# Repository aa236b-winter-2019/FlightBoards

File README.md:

# FlightBoards
Home of PCB Designs

### Notes: 
* Commit 2427577 Contains Motherboard, Solar Panel X and Solar Panel Y documents that correspond to first revision of these boards
* Commit daf960a contains Solar Panel Z documents that correspond to first revision

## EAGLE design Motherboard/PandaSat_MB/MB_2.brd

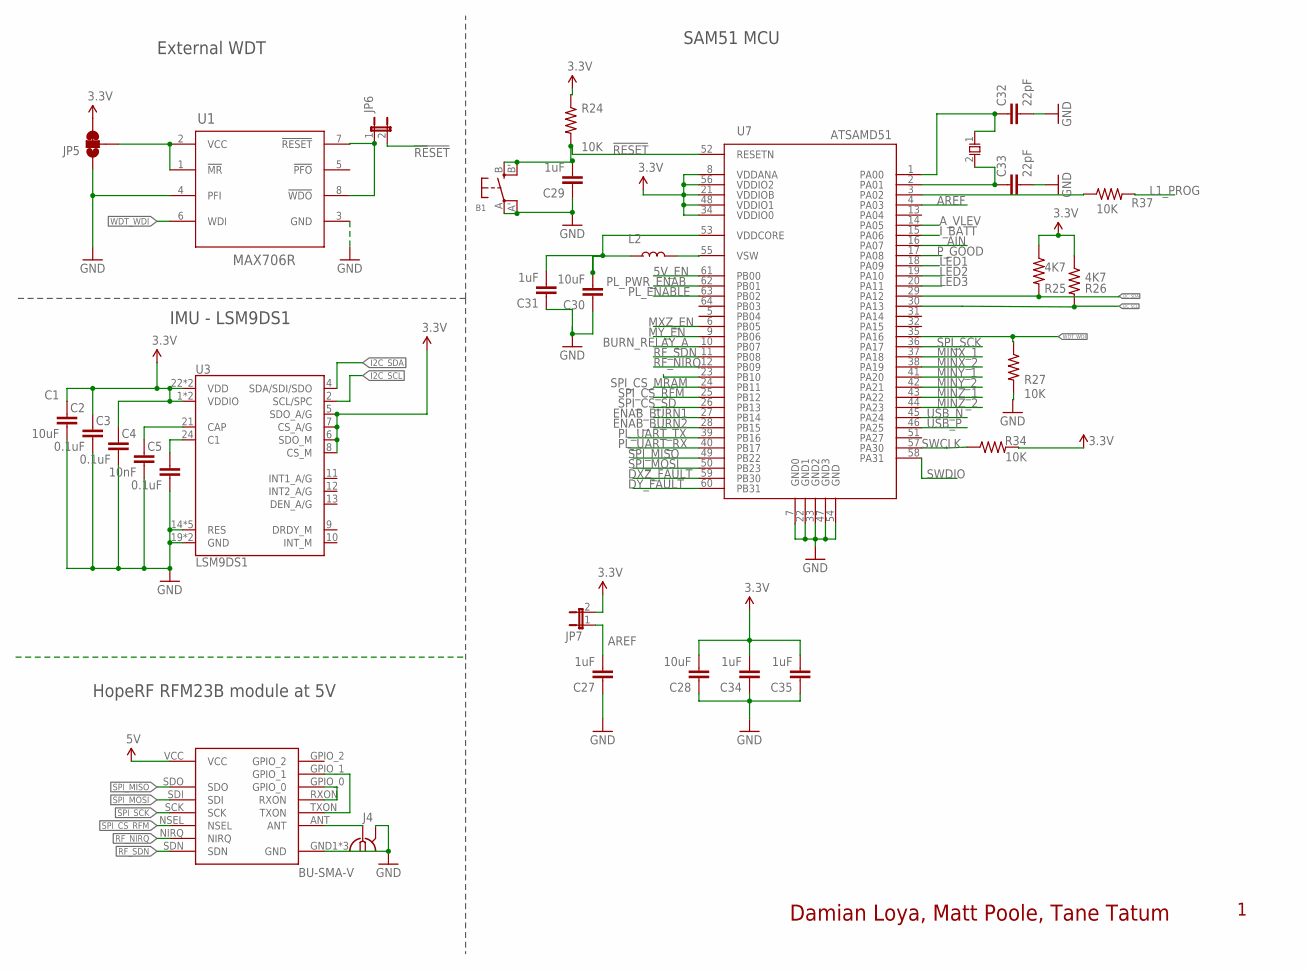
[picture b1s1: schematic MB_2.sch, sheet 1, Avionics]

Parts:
B1: SWITCH_TACT_SMT4.6X2.8; BTN_KMR2_4.6X2.8
C1: 10uF; 0603-CAP
C2, C3, C5: 0.1uF; 0603-CAP
C4: 10nF; 0603-CAP
C27, C29, C31, C34, C35: 1uF; C0603
C28, C30: 10uF; C0603
C32, C33: 22pF; C0603
J4: BU-SMA-V
JP5: JUMPER-PAD-3-2OF3_NC_BY_TRACE_SMALL; PAD-JUMPER-3-2OF3_NC_BY_TRACE_YES_SILK_FULL_BOX
JP6, JP7: JP1E; JP1
L2: 10uH; 1210
R24, R27, R34, R37: 10K; R0603
R25, R26: 4K7; R0603
U1: MAX706R; SO8
U3: LSM9DS1; LGA24-8X4
U5: RFM23BP
U7: ATSAMD51; TQFP-64
X1: ECX-31B

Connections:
3.3V: C1.1, C2.1, C3.1, C28.2, C34.2, C35.2, JP5.3, JP7.2, R24.1, R25.1, R26.1, R34.2, U3.1 (VDDIO), U3.3 (VDDIO), U3.5 (SDO_A/G), U3.6 (SDO_M), U3.7 (CS_A/G), U3.8 (CS_M), U3.22 (VDD), U3.23 (VDD), U7.8 (VDDANA), U7.21 (VDDIOB), U7.34 (VDDIO0), U7.48 (VDDIO1), U7.56 (VDDIO2); also elsewhere on the board
5V: U5.VCC; also elsewhere on the board
5V_EN: U7.61 (PB00); also elsewhere on the board
!RESET: B1.B (S), B1.B' (S1), C29.2, JP6.2, R24.2, U7.52 (RESETN); also elsewhere on the board
AIN: U7.16 (PA07)
AREF: C27.2, JP7.1, U7.4 (PA03)
A_VLEV: U7.14 (PA05); also elsewhere on the board
BURN_RELAY_A: U7.10 (PB07); also elsewhere on the board
DXZ_FAULT: U7.59 (PB30); also elsewhere on the board
DY_FAULT: U7.60 (PB31); also elsewhere on the board
ENAB_BURN1: U7.27 (PB14); also elsewhere on the board
ENAB_BURN2: U7.28 (PB15); also elsewhere on the board
GND: B1.A, B1.A' (P1), C1.2, C2.2, C3.2, C4.2, C5.2, C27.1, C28.1, C29.1, C30.1, C31.1, C32.2, C33.2, C34.1, C35.1, J4.2, J4.3 (2), J4.4 (2), J4.5 (2), JP5.1, R27.2, U1.3 (GND), U1.4 (PFI), U3.14 (RES), U3.15 (RES), U3.16 (RES), U3.17 (RES), U3.18 (RES), U3.19 (GND), U3.20 (GND), U5.GND1 (GND), U5.GND2 (GND), U5.GND3 (GND), U7.7 (GND0), U7.22 (GND1), U7.33 (GND2), U7.47 (GND3), U7.54 (GND); also elsewhere on the board
I2C_SCL: R26.2, U3.2 (SCL/SPC), U7.30 (PA13)
I2C_SDA: R25.2, U3.4 (SDA/SDI/SDO), U7.29 (PA12)
I_BATT: U7.15 (PA06); also elsewhere on the board
L1_PROG: R37.2; also elsewhere on the board
LED1: U7.18 (PA09); also elsewhere on the board
LED2: U7.19 (PA10); also elsewhere on the board
LED3: U7.20 (PA11); also elsewhere on the board
LED4: U7.23 (PB10); also elsewhere on the board
MINX_1: U7.37 (PA18); also elsewhere on the board
MINX_2: U7.38 (PA19); also elsewhere on the board
MINY_1: U7.41 (PA20); also elsewhere on the board
MINY_2: U7.42 (PA21); also elsewhere on the board
MINZ_1: U7.43 (PA22); also elsewhere on the board
MINZ_2: U7.44 (PA23); also elsewhere on the board
MXZ_EN: U7.6 (PB05); also elsewhere on the board
MY_EN: U7.9 (PB06); also elsewhere on the board
unnamed: JP6.1, U1.7 (!RESET), U1.8 (!WDO)
unnamed: C4.1, U3.21 (CAP)
unnamed: C5.1, U3.24 (C1)
unnamed: JP5.2, U1.1 (!MR), U1.2 (VCC)
unnamed: L2.2, U7.55 (VSW)
unnamed: C32.1, U7.1 (PA00), X1.1
unnamed: J4.1, U5.ANT
unnamed: U5.GPIO_0, U5.RXON
unnamed: U5.GPIO_1, U5.TXON
unnamed: C30.2, C31.2, L2.1, U7.53 (VDDCORE)
unnamed: C33.1, U7.2 (PA01), X1.2
unnamed: R37.1, U7.3 (PA02)
PL_ENABLE: U7.63 (PB02); also elsewhere on the board
PL_PWR_ENAB: U7.62 (PB01); also elsewhere on the board
PL_UART_RX: U7.40 (PB17); also elsewhere on the board
PL_UART_TX: U7.39 (PB16); also elsewhere on the board
P_GOOD: U7.17 (PA08); also elsewhere on the board
RF_NIRQ: U5.NIRQ, U7.12 (PB09)
RF_SDN: U5.SDN, U7.11 (PB08)
SPI_CS_MRAM: U7.24 (PB11); also elsewhere on the board
SPI_CS_RFM: U5.NSEL, U7.25 (PB12)
SPI_CS_SD: U7.26 (PB13); also elsewhere on the board
SPI_MISO: U5.SDO, U7.49 (PB22); also elsewhere on the board
SPI_MOSI: U5.SDI, U7.50 (PB23); also elsewhere on the board
SPI_SCK: U5.SCK, U7.36 (PA17); also elsewhere on the board
SWCLK: R34.1, U7.57 (PA30); also elsewhere on the board
SWDIO: U7.58 (PA31); also elsewhere on the board
USB_N: U7.45 (PA24); also elsewhere on the board
USB_P: U7.46 (PA25); also elsewhere on the board
WDT_WDI: R27.1, U1.6 (WDI), U7.35 (PA16)

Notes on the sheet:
IMU - LSM9DS1
External WDT
HopeRF RFM23B module at 5V
SAM51 MCU
Damian Loya, Matt Poole, Tane Tatum

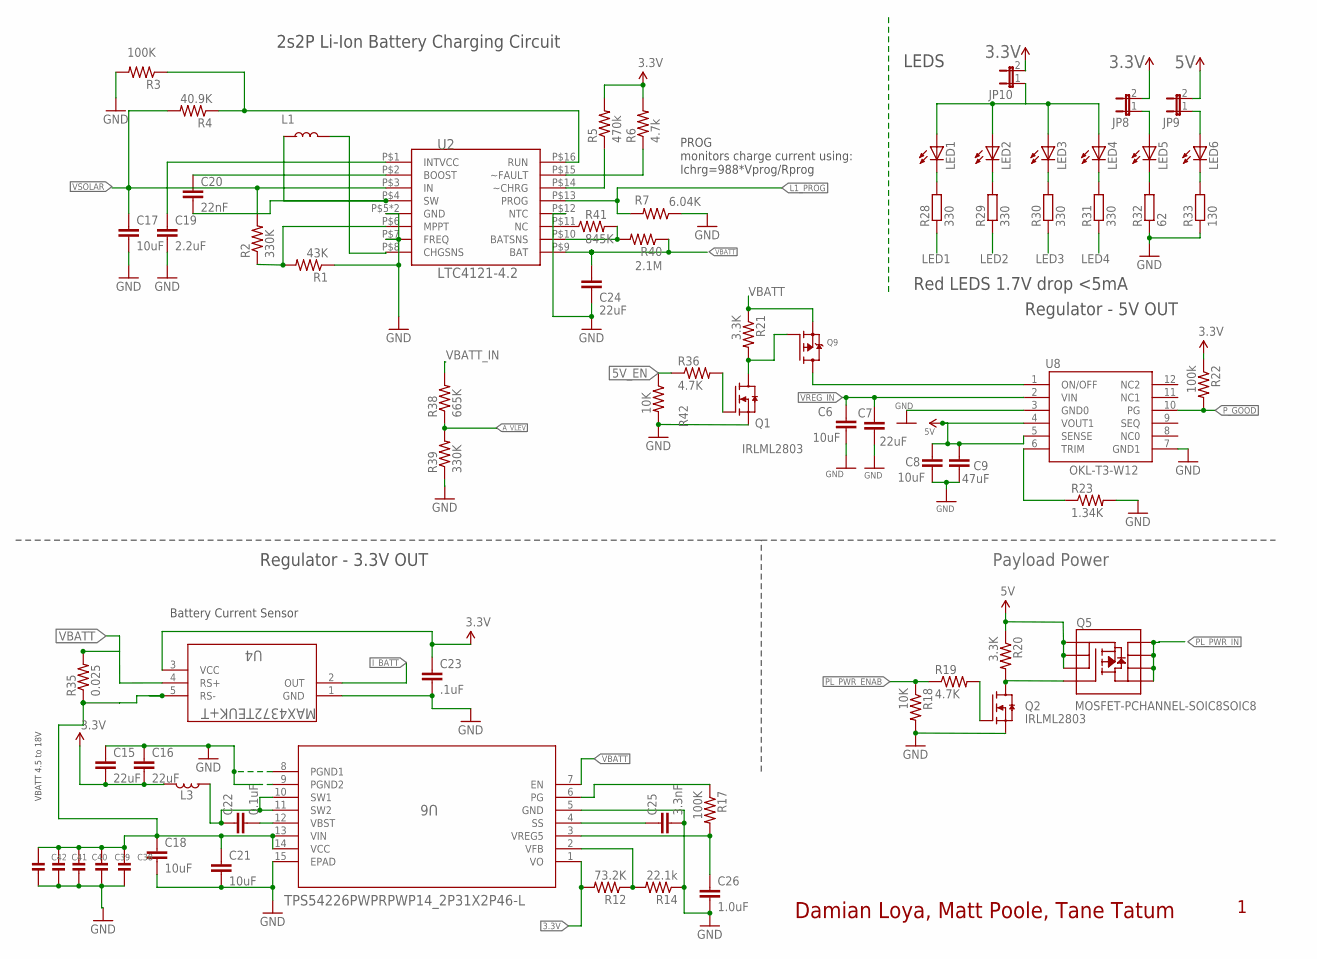
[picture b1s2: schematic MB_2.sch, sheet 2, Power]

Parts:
C6, C8, C17, C18, C21: 10uF; 0603
C7, C24: 22uF; 0603
C9: 47uF; 0603
C15, C16: 22uF; 0805
C19: 2.2uF; 0603
C20: 22nF; 0603
C22: 0.1uF; 0603
C23: .1uF; 0603-CAP
C25: 3.3nF; 0603
C26: 1.0uF; 0603
C38, C39, C40, C41, C42: CAP_CERAMIC1206; 1206
JP8, JP9, JP10: JP1E; JP1
L1: 56uH; 1210
L3: 3.3uH; 1210
LED1, LED2, LED3, LED4, LED5, LED6: LEDCHIP-LED0603; CHIP-LED0603
Q1, Q2: IRLML2803; SOT-23
Q5: MOSFET-PCHANNEL-SOIC8SOIC8; SO08
Q9: MOSFET-PWIDE; SOT23-WIDE
R1: 43K; R0603
R2, R39: 330K; R0603
R3, R17: 100K; R0603
R4: 40.9K; R0603
R5: 470k; R0603
R6: 4.7k; R0603
R7: 6.04K; R0603
R12: 73.2K; R0603
R14: 22.1k; R0603
R18, R42: 10K; R0603
R19, R36: 4.7K; R0603
R20, R21: 3.3K; R0603
R22: 100k; R0603
R23: 1.34K; R0603
R28, R29, R30, R31: 330; R0603
R32: 62; R0603
R33: 130; R0603
R35: 0.025; R1210
R38: 665K; R0603
R40: 2.1M; R0603
R41: 845K; R0603
U2: LTC4121-4.2; QFN-16-PAD
U4: MAX4372TEUK+T; 21-0057F
U6: TPS54226PWPRPWP14_2P31X2P46-L; PWP14_2P31X2P46-L
U8: OKL-T3-W12

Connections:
3.3V: C15.2, C16.2, C23.1, JP8.2, JP10.2, L3.2, R5.2, R6.2, R12.2, R22.1, U4.3 (VCC), U6.1 (VO); also elsewhere on the board
5V: C8.1, C9.1, JP9.2, Q5.1 (S), Q5.2 (S), Q5.3 (S), R20.1, U8.4 (VOUT1), U8.5 (SENSE); also elsewhere on the board
5V_EN: R36.1, R42.1; also elsewhere on the board
A_VLEV: R38.1, R39.2; also elsewhere on the board
GND: C6.2, C7.2, C8.2, C9.2, C15.1, C16.1, C17.2, C18.2, C19.2, C21.2, C23.2, C24.2, C25.2, C26.2, C38.2, C39.2, C40.2, C41.2, C42.2, Q1.2 (S), Q2.2 (S), R1.1, R3.2, R7.1, R14.1, R18.2, R23.2, R32.1, R33.1, R39.1, R42.2, U2.P$5 (GND), U2.P$7 (FREQ), U2.P$12 (NTC), U2.P$17 (GND), U4.1 (GND), U6.5 (GND), U6.8 (PGND1), U6.9 (PGND2), U6.15 (EPAD), U8.3 (GND0), U8.7 (GND1); also elsewhere on the board
I_BATT: U4.2 (OUT); also elsewhere on the board
L1_CHG: R3.1, R4.1, U2.P$16 (RUN)
L1_FAULTN: R6.1, U2.P$15 (~FAULT)
L1_PROG: R7.2, U2.P$13 (PROG); also elsewhere on the board
LED1: R28.1; also elsewhere on the board
LED2: R29.1; also elsewhere on the board
LED3: R30.1; also elsewhere on the board
LED4: R31.1; also elsewhere on the board
unnamed: C22.1, L3.1, U6.10 (SW1), U6.11 (SW2)
unnamed: L1.2, U2.P$8 (CHGSNS)
unnamed: C20.2, L1.1, U2.P$4 (SW)
unnamed: C20.1, U2.P$2 (BOOST)
unnamed: Q2.1 (G), R19.2
unnamed: C19.1, U2.P$1 (INTVCC)
unnamed: Q2.3 (D), Q5.4 (G), R20.2
unnamed: R1.2, R2.1, U2.P$6 (MPPT)
unnamed: C22.2, U6.12 (VBST)
unnamed: R5.1, U2.P$14 (~CHRG)
unnamed: R40.2, R41.2, U2.P$10 (BATSNS)
unnamed: Q1.3 (D), Q9.1 (G), R21.2
unnamed: R23.1, U8.6 (TRIM)
unnamed: Q1.1 (G), R36.2
unnamed: LED1.C, R28.2
unnamed: Q9.3 (D), U8.1 (ON/OFF)
unnamed: LED2.C, R29.2
unnamed: C26.1, R17.2, U6.3 (VREG5)
unnamed: LED3.C, R30.2
unnamed: LED4.C, R31.2
unnamed: LED5.C, R32.2
unnamed: LED6.C, R33.2
unnamed: C25.1, U6.4 (SS)
unnamed: R12.1, R14.2, U6.2 (VFB)
unnamed: JP8.1, LED5.A
unnamed: R41.1, U2.P$11 (NC)
unnamed: JP9.1, LED6.A
unnamed: JP10.1, LED1.A, LED2.A, LED3.A, LED4.A
PGOOD: R17.1, U6.6 (PG)
PL_PWR_ENAB: R18.1, R19.1; also elsewhere on the board
PL_PWR_IN: Q5.5 (D), Q5.6 (D), Q5.7 (D), Q5.8 (D); also elsewhere on the board
P_GOOD: R22.2, U8.10 (PG); also elsewhere on the board
VBATT: C24.1, Q9.2 (S), R21.1, R35.2, R40.1, U2.P$9 (BAT), U4.4 (RS+), U6.7 (EN); also elsewhere on the board
VBATT_IN: R38.2; also elsewhere on the board
VREG_IN: C6.1, C7.1, C18.1, C21.1, C38.1, C39.1, C40.1, C41.1, C42.1, R35.1, U4.5 (RS-), U6.13 (VIN), U6.14 (VCC), U8.2 (VIN)
VSOLAR: C17.1, R2.2, R4.2, U2.P$3 (IN); also elsewhere on the board

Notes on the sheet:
Battery Current Sensor
Payload Power
Regulator - 3.3V OUT
VBATT 4.5 to 18V
Regulator - 5V OUT
2s2P Li-Ion Battery Charging Circuit
PROG monitors charge current using: Ichrg=988*Vprog/Rprog
Damian Loya, Matt Poole, Tane Tatum
LEDS
Red LEDS 1.7V drop <5mA

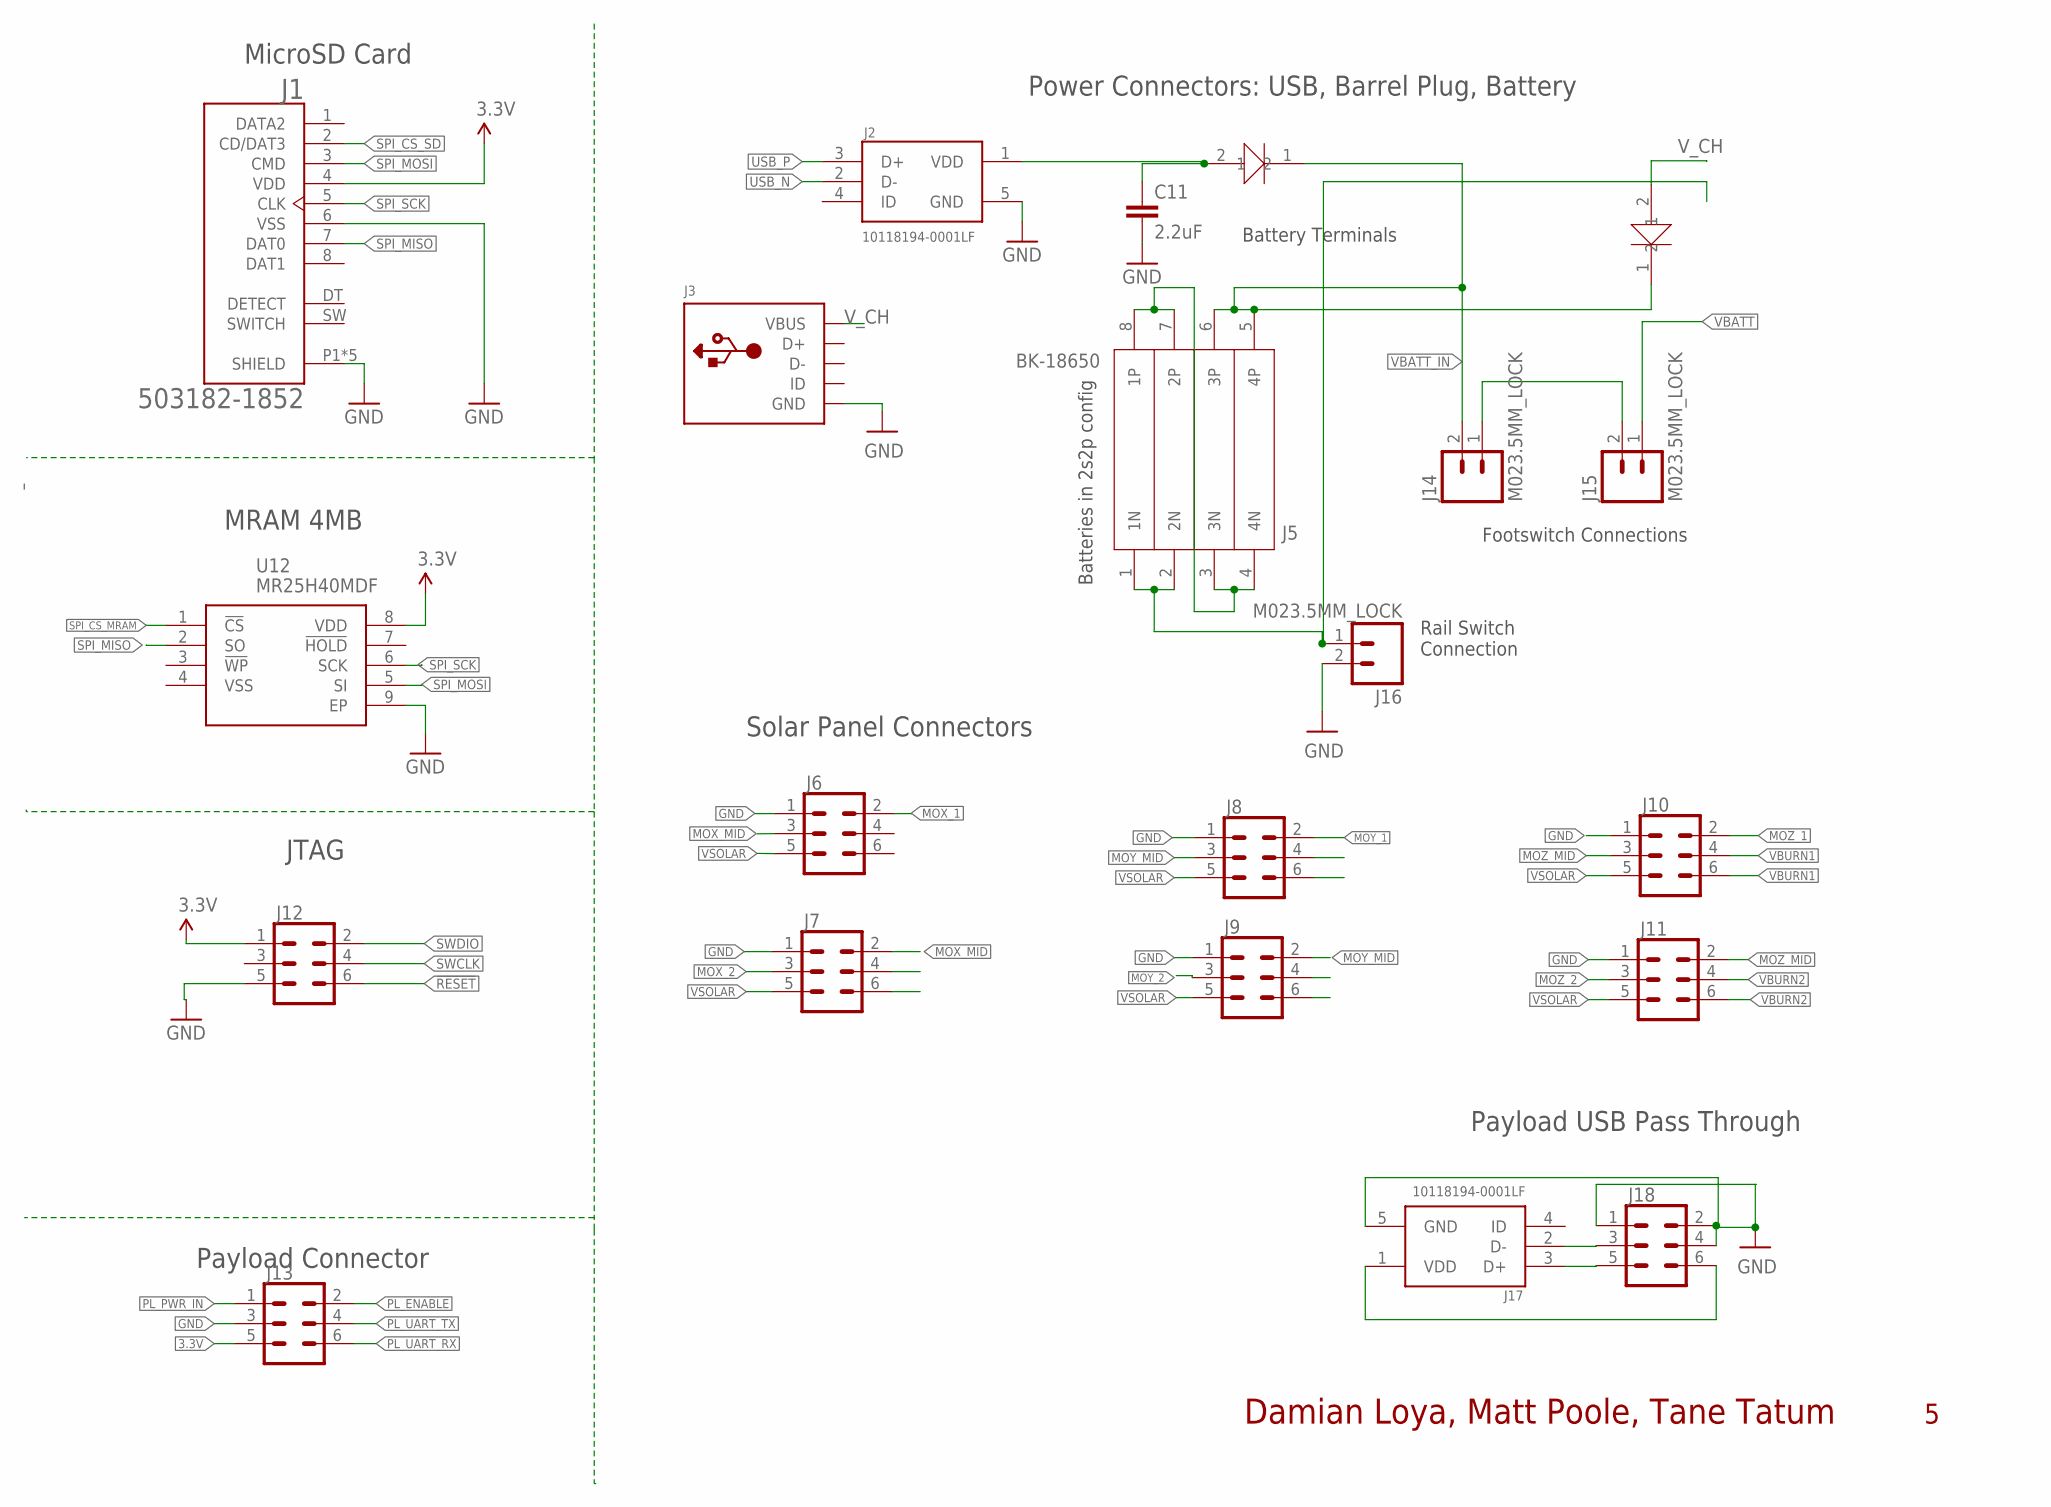
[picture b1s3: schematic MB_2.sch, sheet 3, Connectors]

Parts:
C11: 2.2uF; 0603
D1, D2: RBR5LAM60ATF; SOD-128
J1: 503182-1852; MOLEX_503182-1852
J2, J17: 10118194-0001LF; FRAMATOME_10118194-0001LF
J3: USBMOLEX; USB-MINIB-THM-MOLEX
J5: BK-18650
J6, J7, J8, J9, J10, J11, J12, J13, J18: CONN_03X22X3_SILK_MALE_PTH; 2X3
J14, J15, J16: M023.5MM_LOCK; SCREWTERMINAL-3.5MM-2_LOCK
U12: MR25H40MDF; SON127P600X500X90-9N

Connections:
3.3V: J1.4 (VDD), J12.1, J13.5, U12.8 (VDD); also elsewhere on the board
!RESET: J12.6; also elsewhere on the board
GND: C11.2, J1.6 (VSS), J1.P1 (SHIELD), J1.P2 (SHIELD), J1.P3 (SHIELD), J1.P4 (SHIELD), J1.P5 (SHIELD), J2.5 (GND), J3.GND, J6.1, J7.1, J8.1, J9.1, J10.1, J11.1, J12.5, J13.3, J16.2, J17.5 (GND), J18.1, J18.2, J18.4, U12.9 (EP); also elsewhere on the board
MOX_1: J6.2; also elsewhere on the board
MOX_2: J7.3; also elsewhere on the board
MOX_MID: J6.3, J7.2
MOY_1: J8.2; also elsewhere on the board
MOY_2: J9.3; also elsewhere on the board
MOY_MID: J8.3, J9.2
MOZ_1: J10.2; also elsewhere on the board
MOZ_2: J11.3; also elsewhere on the board
MOZ_MID: J10.3, J11.2
unnamed: J14.1, J15.2
unnamed: C11.1, D2.2, J2.1 (VDD)
unnamed: J17.2 (D-), J18.3
unnamed: J17.3 (D+), J18.5
unnamed: J17.1 (VDD), J18.6
unnamed: J5.3 (3N), J5.4 (4N), J5.7 (2P), J5.8 (1P)
unnamed: J5.1 (1N), J5.2 (2N), J16.1
PL_ENABLE: J13.2; also elsewhere on the board
PL_PWR_IN: J13.1; also elsewhere on the board
PL_UART_RX: J13.6; also elsewhere on the board
PL_UART_TX: J13.4; also elsewhere on the board
SPI_CS_MRAM: U12.1 (!CS); also elsewhere on the board
SPI_CS_SD: J1.2 (CD/DAT3); also elsewhere on the board
SPI_MISO: J1.7 (DAT0), U12.2 (SO); also elsewhere on the board
SPI_MOSI: J1.3 (CMD), U12.5 (SI); also elsewhere on the board
SPI_SCK: J1.5 (CLK), U12.6 (SCK); also elsewhere on the board
SWCLK: J12.4; also elsewhere on the board
SWDIO: J12.2; also elsewhere on the board
USB_N: J2.2 (D-); also elsewhere on the board
USB_P: J2.3 (D+); also elsewhere on the board
VBATT: J15.1; also elsewhere on the board
VBATT_IN: D1.1, D2.1, J5.5 (4P), J5.6 (3P), J14.2; also elsewhere on the board
VBURN1: J10.4, J10.6; also elsewhere on the board
VBURN2: J11.4, J11.6; also elsewhere on the board
VSOLAR: J6.5, J7.5, J8.5, J9.5, J10.5, J11.5; also elsewhere on the board
V_CH: D1.2, J3.VBUS

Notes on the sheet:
Damian Loya, Matt Poole, Tane Tatum
JTAG
Power Connectors: USB, Barrel Plug, Battery
MicroSD Card
MRAM 4MB
Footswitch Connections
Battery Terminals
Rail Switch Connection
Solar Panel Connectors
Payload Connector
Batteries in 2s2p config
Payload USB Pass Through

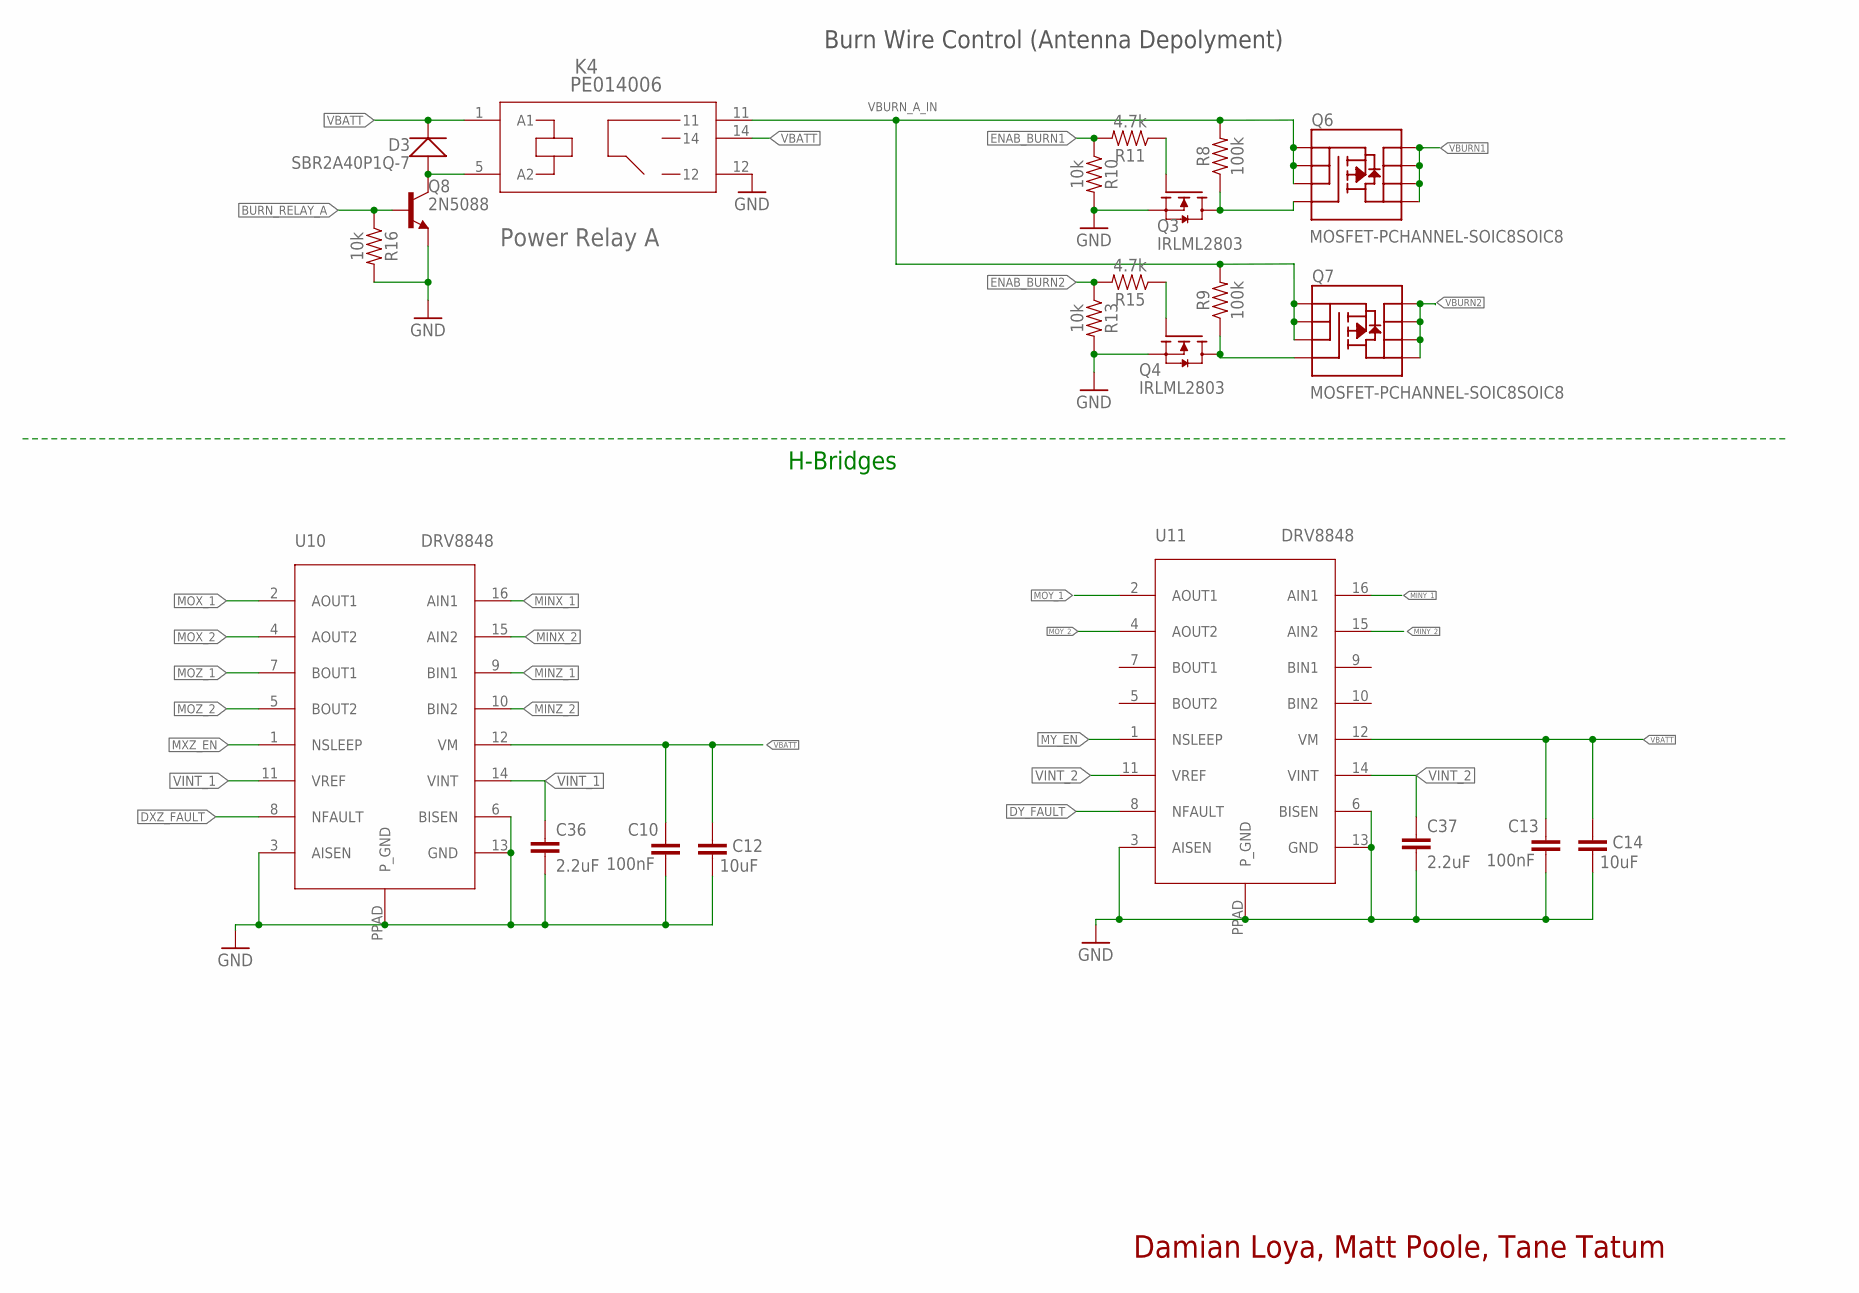
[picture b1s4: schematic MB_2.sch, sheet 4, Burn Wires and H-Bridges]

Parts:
C10, C13: 100nF; 0603
C12, C14: 10uF; 0603
C36, C37: 2.2uF; 0603-CAP; VOLTAGE 6.3V
D3: SBR2A40P1Q-7; PWRDI-123
K4: PE014006; RELAY5-PE_CO
Q3, Q4: IRLML2803; SOT-23
Q6, Q7: MOSFET-PCHANNEL-SOIC8SOIC8; SO08
Q8: 2N5088; SOT23
R8, R9: 100k; 0603
R10, R13, R16: 10k; 0603
R11, R15: 4.7k; 0603
U10, U11: DRV8848; HTSSOP

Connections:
BURN_RELAY_A: Q8.1 (B), R16.1; also elsewhere on the board
DXZ_FAULT: U10.8 (NFAULT); also elsewhere on the board
DY_FAULT: U11.8 (NFAULT); also elsewhere on the board
ENAB_BURN1: R10.1, R11.2; also elsewhere on the board
ENAB_BURN2: R13.1, R15.2; also elsewhere on the board
GND: C10.2, C12.2, C13.2, C14.2, C36.2, C37.2, K4.12, Q3.2 (S), Q4.2 (S), Q8.2 (E), R10.2, R13.2, R16.2, U10.3 (AISEN), U10.6 (BISEN), U10.13 (GND), U10.PPAD (P_GND), U11.3 (AISEN), U11.6 (BISEN), U11.13 (GND), U11.PPAD (P_GND); also elsewhere on the board
MINX_1: U10.16 (AIN1); also elsewhere on the board
MINX_2: U10.15 (AIN2); also elsewhere on the board
MINY_1: U11.16 (AIN1); also elsewhere on the board
MINY_2: U11.15 (AIN2); also elsewhere on the board
MINZ_1: U10.9 (BIN1); also elsewhere on the board
MINZ_2: U10.10 (BIN2); also elsewhere on the board
MOX_1: U10.2 (AOUT1); also elsewhere on the board
MOX_2: U10.4 (AOUT2); also elsewhere on the board
MOY_1: U11.2 (AOUT1); also elsewhere on the board
MOY_2: U11.4 (AOUT2); also elsewhere on the board
MOZ_1: U10.7 (BOUT1); also elsewhere on the board
MOZ_2: U10.5 (BOUT2); also elsewhere on the board
MXZ_EN: U10.1 (NSLEEP); also elsewhere on the board
MY_EN: U11.1 (NSLEEP); also elsewhere on the board
unnamed: Q3.3 (D), Q6.4 (G), R8.1
unnamed: Q3.1 (G), R11.1
unnamed: Q4.1 (G), R15.1
unnamed: D3.A, K4.5 (A2), Q8.3 (C)
unnamed: Q4.3 (D), Q7.4 (G), R9.1
VBATT: C10.1, C12.1, C13.1, C14.1, D3.C, K4.1 (A1), K4.14, U10.12 (VM), U11.12 (VM); also elsewhere on the board
VBURN1: Q6.5 (D), Q6.6 (D), Q6.7 (D), Q6.8 (D); also elsewhere on the board
VBURN2: Q7.5 (D), Q7.6 (D), Q7.7 (D), Q7.8 (D); also elsewhere on the board
VBURN_A_IN: K4.11, Q6.1 (S), Q6.2 (S), Q6.3 (S), Q7.1 (S), Q7.2 (S), Q7.3 (S), R8.2, R9.2
VINT_1: C36.1, U10.11 (VREF), U10.14 (VINT)
VINT_2: C37.1, U11.11 (VREF), U11.14 (VINT)

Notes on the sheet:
Power Relay A
Burn Wire Control (Antenna Depolyment)
H-Bridges
Damian Loya, Matt Poole, Tane Tatum

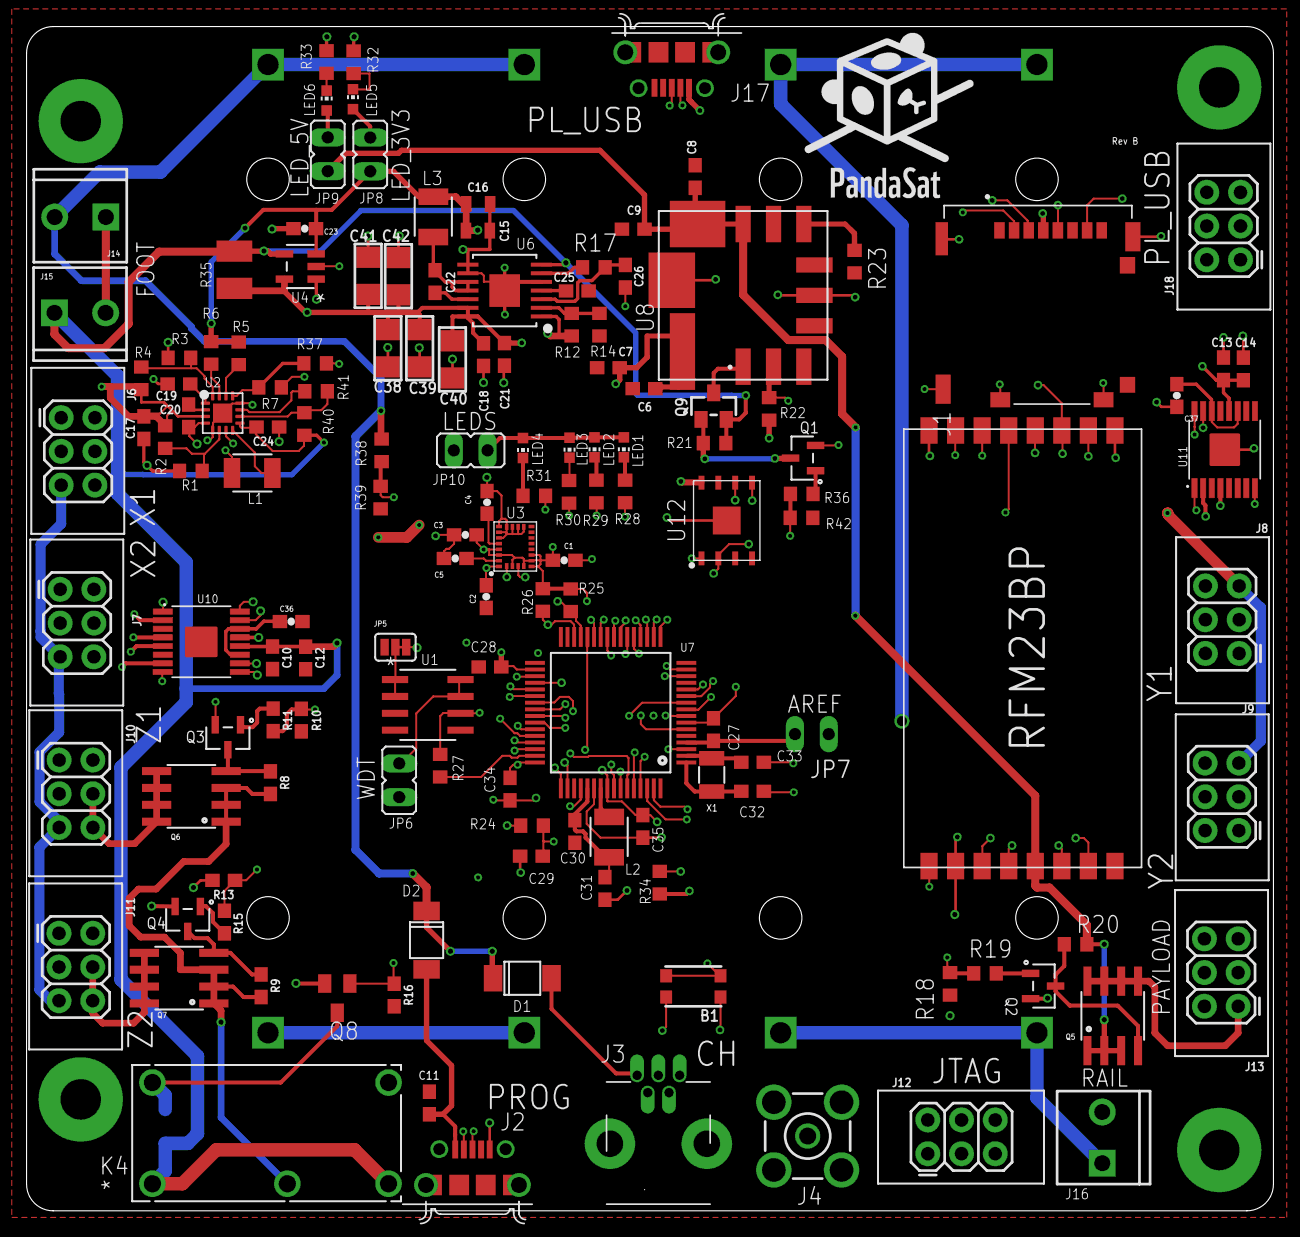
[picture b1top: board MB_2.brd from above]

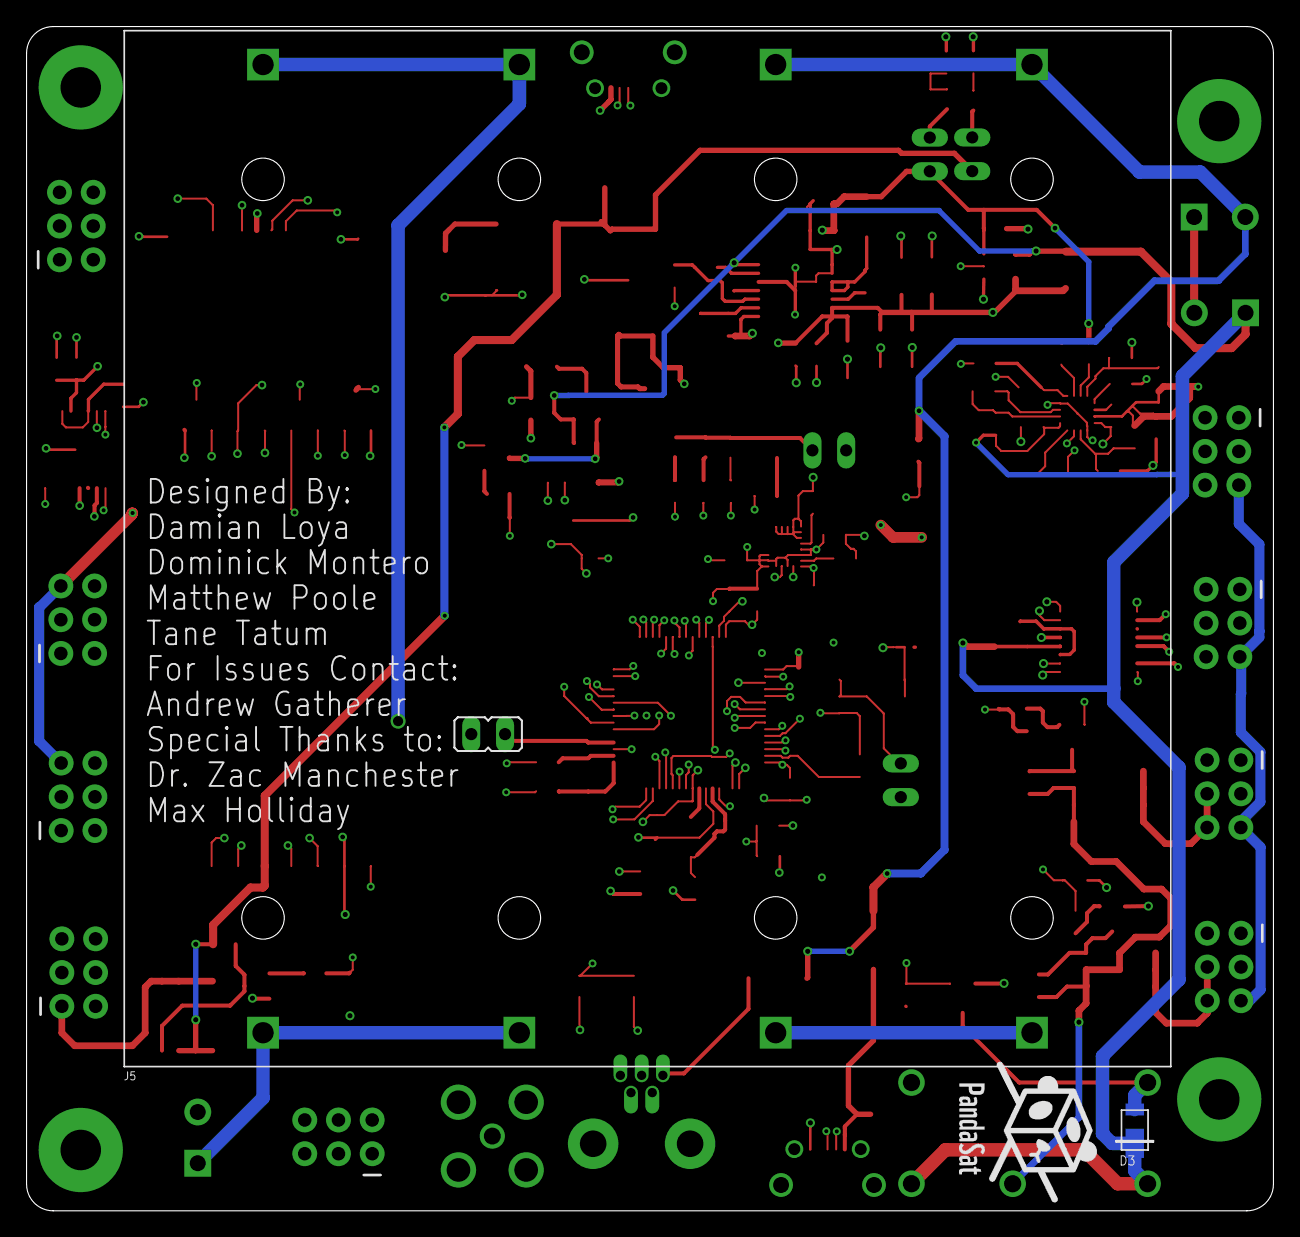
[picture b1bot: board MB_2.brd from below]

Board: 4 copper layers, 93.9 x 89.2 mm, 143 parts (3 on the bottom side), 121 nets.

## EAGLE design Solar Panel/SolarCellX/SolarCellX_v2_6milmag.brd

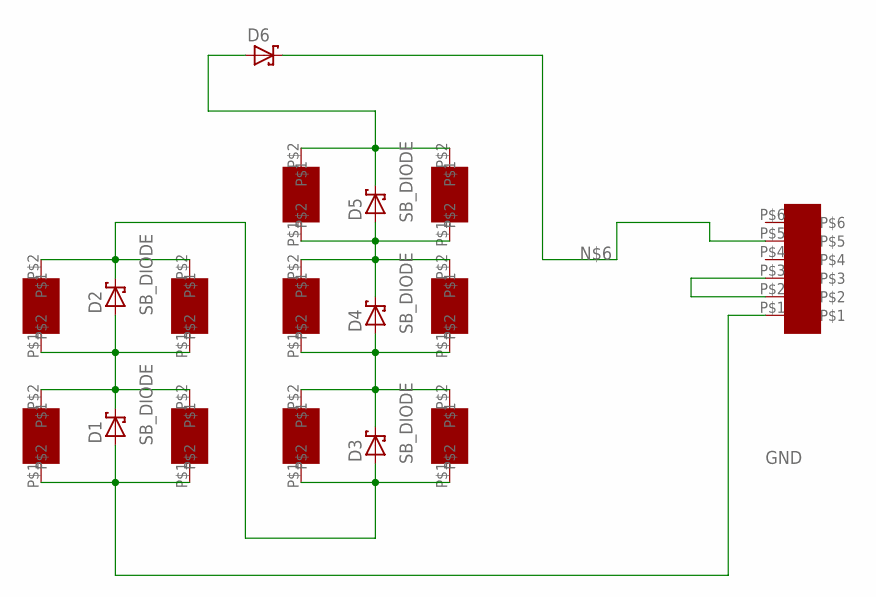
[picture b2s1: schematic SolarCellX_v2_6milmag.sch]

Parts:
1, 2, 11, 12, 13, 14, 21, 22, 23, 24: SLMD121H04L
D1, D2, D3, D4, D5, D6: SB_DIODE
U$1: M20-8760342

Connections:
GND: 11.P$1, 12.P$1, D1.POS, U$1.P$1
unnamed: U$1.P$2, U$1.P$3
unnamed: 11.P$2, 12.P$2, 13.P$1, 14.P$1, D1.NEG, D2.POS
unnamed: 13.P$2, 14.P$2, 21.P$1, 22.P$1, D2.NEG, D3.POS
unnamed: 1.P$1, 2.P$1, 23.P$2, 24.P$2, D4.NEG, D5.POS
unnamed: 21.P$2, 22.P$2, 23.P$1, 24.P$1, D3.NEG, D4.POS
unnamed: D6.NEG, U$1.P$5
V_SOLAR: 1.P$2, 2.P$2, D5.NEG, D6.POS

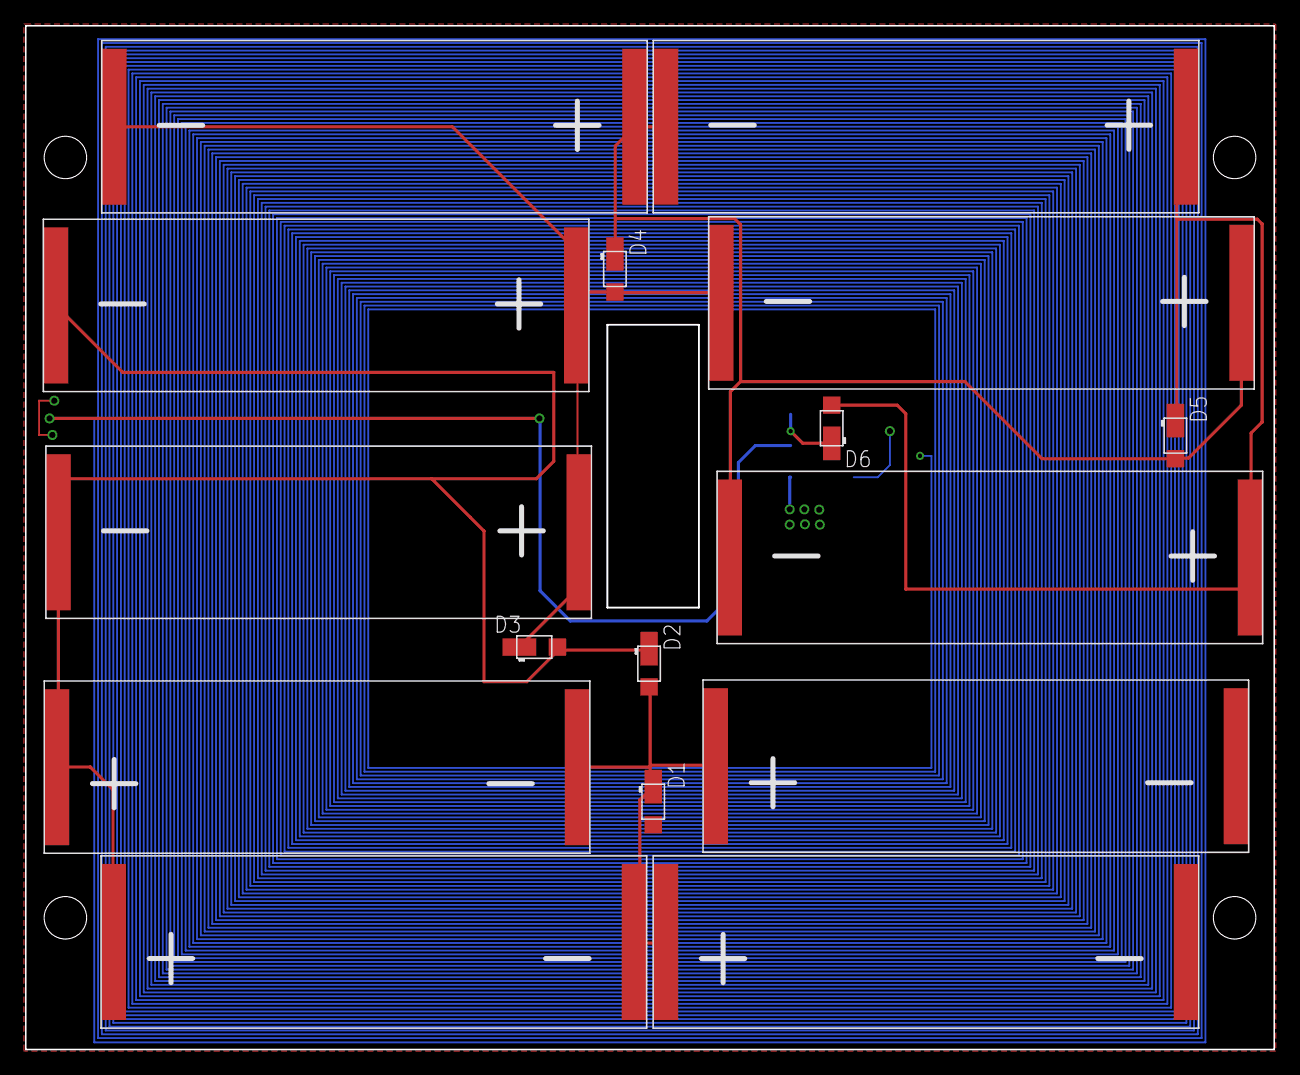
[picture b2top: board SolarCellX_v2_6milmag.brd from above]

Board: 4 copper layers, 100.0 x 82.0 mm, 17 parts (1 on the bottom side), 8 nets.

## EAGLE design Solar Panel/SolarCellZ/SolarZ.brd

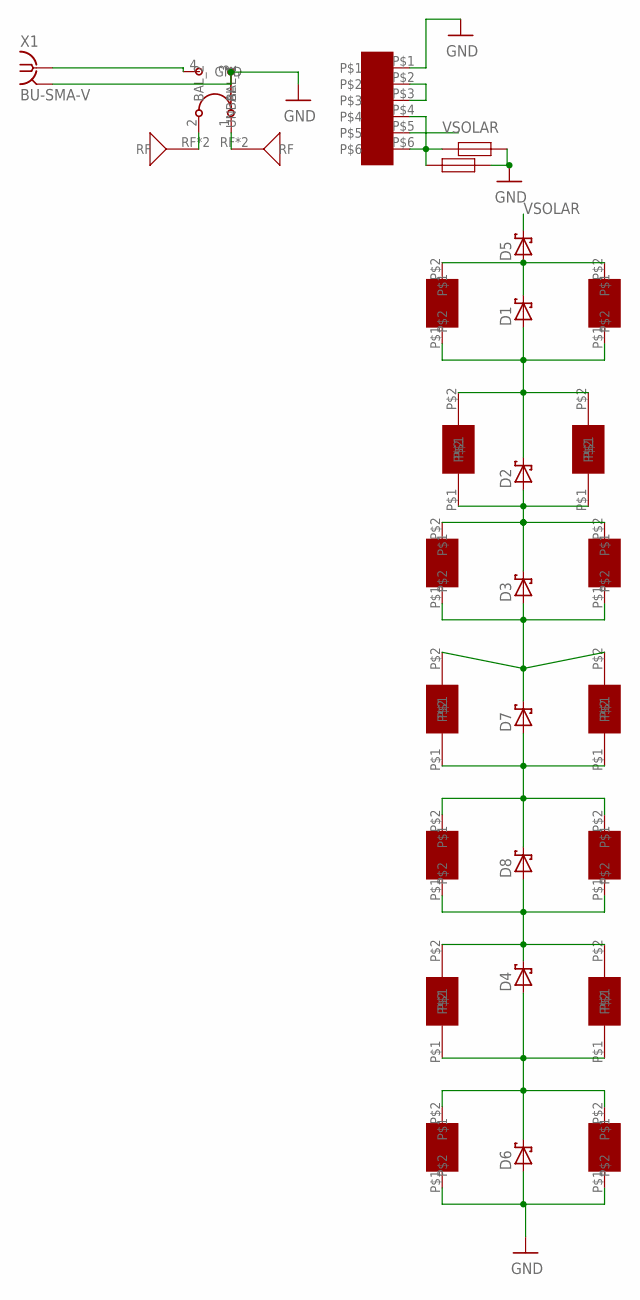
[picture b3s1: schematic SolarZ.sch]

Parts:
1, 6, 7, 10, 11, 13: KXOB22-04X3F
2, 3, 4, 5, 8, 9, 12, 14: SLMD121H04L
D1, D2, D3, D4, D5, D6, D7, D8: SB_DIODE
F1, F2: BURN_TERM; BURN_WIRE
U$1: BALUN
U$2, U$3: ANTENNA; TAPE
U$4: M20-8760342
X1: BU-SMA-V

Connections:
GND: 8.P$1, 9.P$1, D6.POS, F1.2, F1.20 (2), F1.200 (2), F2.2, F2.20 (2), F2.200 (2), U$1.3 (UNBAL), U$4.P$1, X1.2, X1.3 (2), X1.4 (2), X1.5 (2)
N8: 6.P$2, 7.P$2, 12.P$1, 14.P$1, D4.NEG, D8.POS
unnamed: U$1.2 (BAL_2), U$3.RF, U$3.RF_2
unnamed: U$1.4 (GND), X1.1
unnamed: U$1.1 (BAL_1), U$2.RF, U$2.RF_2
unnamed: 1.P$2, 2.P$1, 3.P$1, 13.P$2, D1.POS, D2.NEG
unnamed: 2.P$2, 3.P$2, D1.NEG, D5.POS
unnamed: U$4.P$2, U$4.P$3
unnamed: 10.P$1, 11.P$1, 12.P$2, 14.P$2, D7.POS, D8.NEG
unnamed: 1.P$1, 4.P$2, 5.P$2, 13.P$1, D2.POS, D3.NEG
unnamed: 6.P$1, 7.P$1, 8.P$2, 9.P$2, D4.POS, D6.NEG
unnamed: 4.P$1, 5.P$1, 10.P$2, 11.P$2, D3.POS, D7.NEG
unnamed: F1.1, F1.10 (1), F1.100 (1), F2.1, F2.10 (1), F2.100 (1), U$4.P$4, U$4.P$6
VSOLAR: D5.NEG, U$4.P$5

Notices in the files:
parts and their libraries:
SparkFun-Capacitors: Licensing: Creative Commons ShareAlike 4.0 International - https://creativecommons.org/licenses/by-sa/4.0
microbuilder: This work is placed in the public domain, and may be freely used for commercial and non-commercial work with the following conditions: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
